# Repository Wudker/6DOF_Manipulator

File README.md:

# Educational 6-DOF Robotic Manipulator – Engineering Thesis

This project presents an educational anthropomorphic robotic manipulator with six degrees of freedom, developed as an engineering thesis. It combines mechanical design, kinematic analysis, embedded control, custom electronics and software development. The system uses an ESP32 and a custom PCB to control six stepper-driven joints through a local web interface. Forward and inverse kinematics provide position control, while repeatability and positioning tests were used to validate the adopted assumptions and identify the prototype’s mechanical limitations.

## Technologies

`ESP32` `C/C++` `Forward kinematics` `Inverse kinematics` `WebServer` `Stepper motors` `DRV8825` `Custom PCB` `Belt transmissions` `3D printing` `CAD`

## Usage and development status

After assembling the hardware and uploading the firmware, the manipulator can be controlled through its local web interface. Before starting movement, verify the wiring, power supply and initial joint positions. The prototype was successfully built and tested; potential improvements include increased mechanical stiffness, more accurate calibration and smoother trajectory planning.

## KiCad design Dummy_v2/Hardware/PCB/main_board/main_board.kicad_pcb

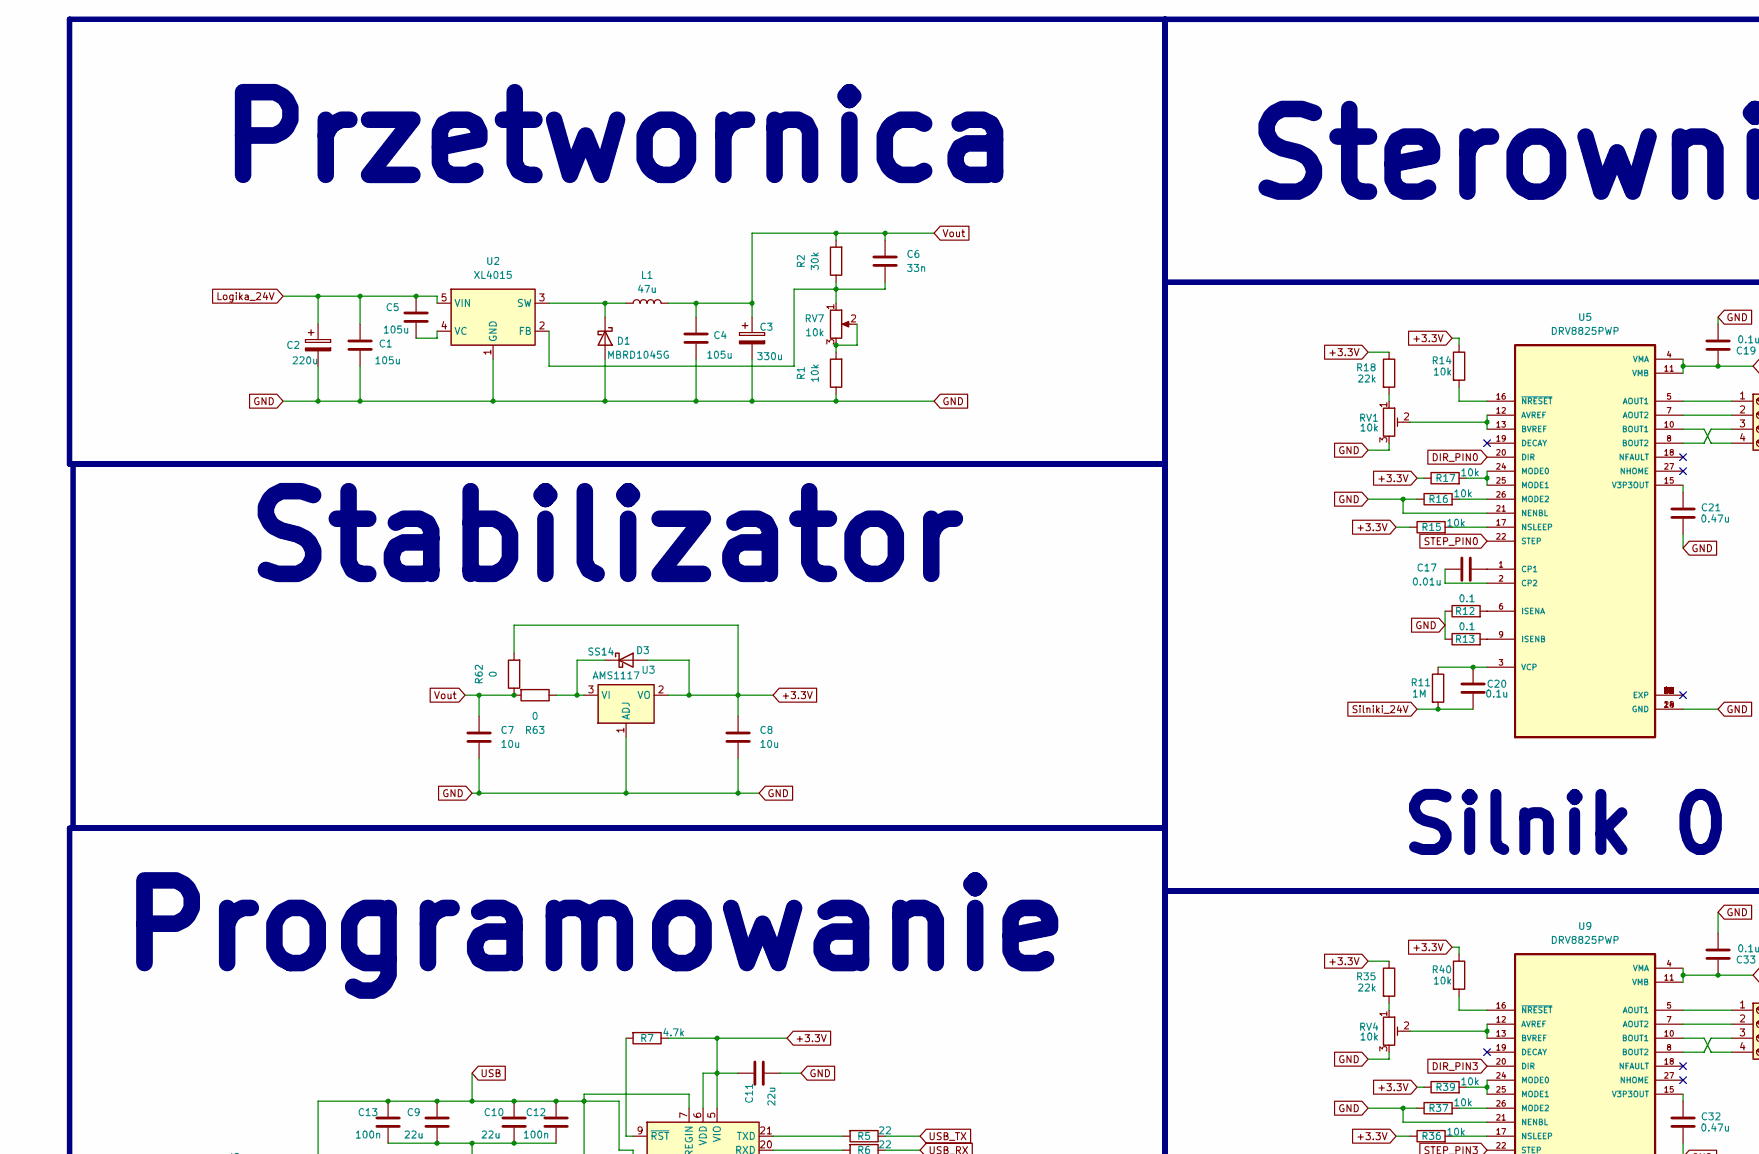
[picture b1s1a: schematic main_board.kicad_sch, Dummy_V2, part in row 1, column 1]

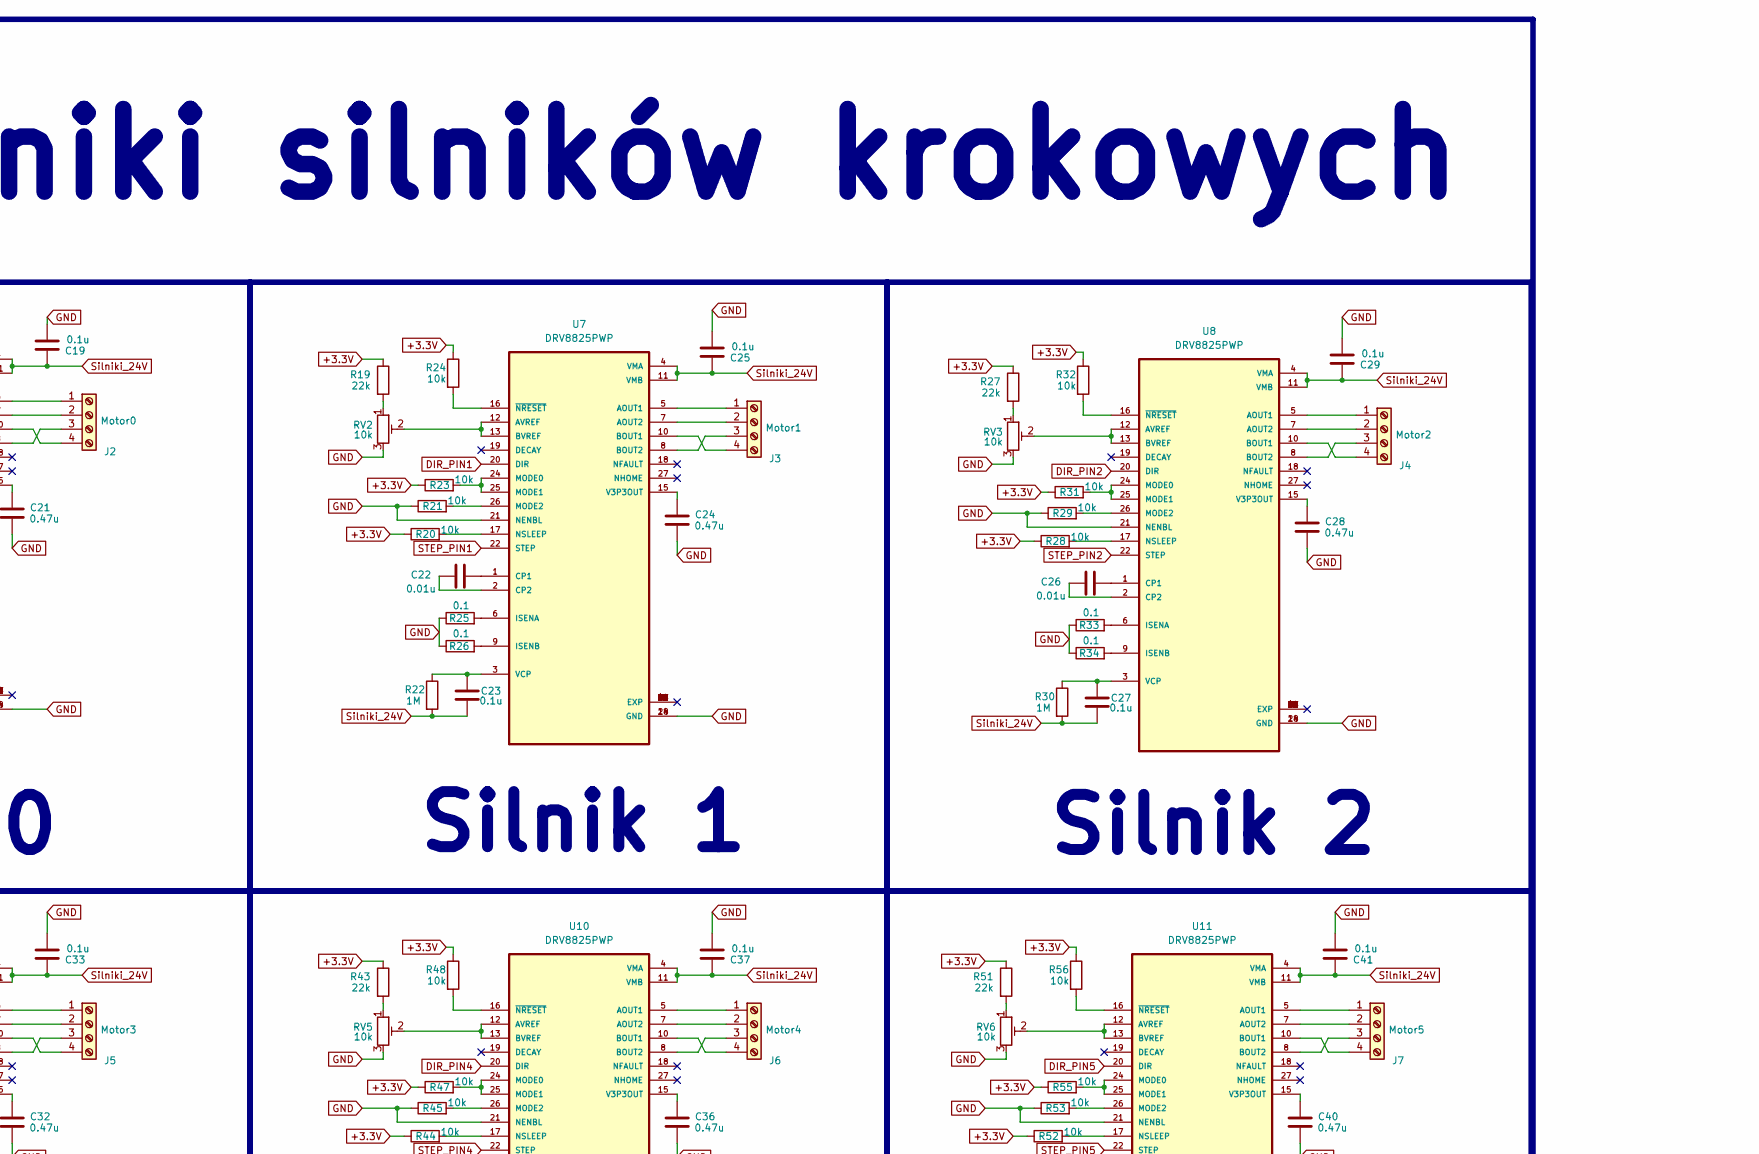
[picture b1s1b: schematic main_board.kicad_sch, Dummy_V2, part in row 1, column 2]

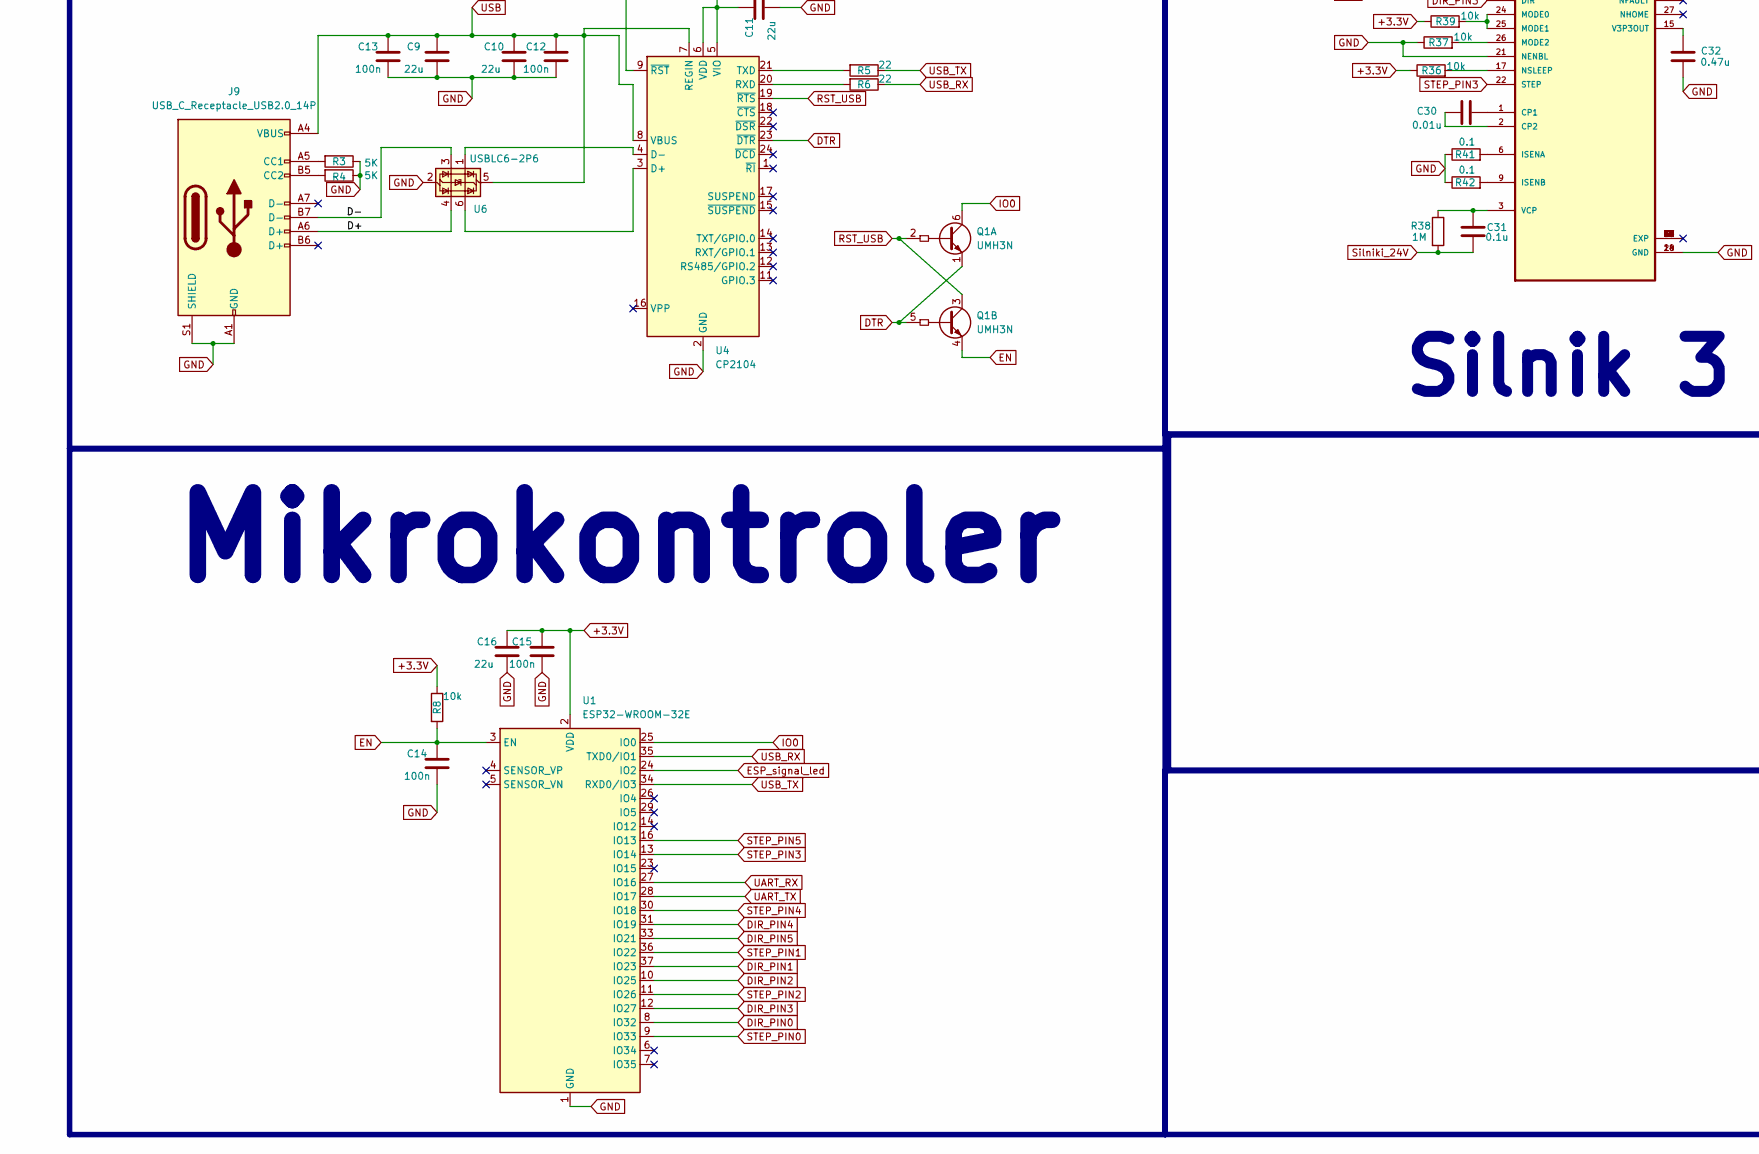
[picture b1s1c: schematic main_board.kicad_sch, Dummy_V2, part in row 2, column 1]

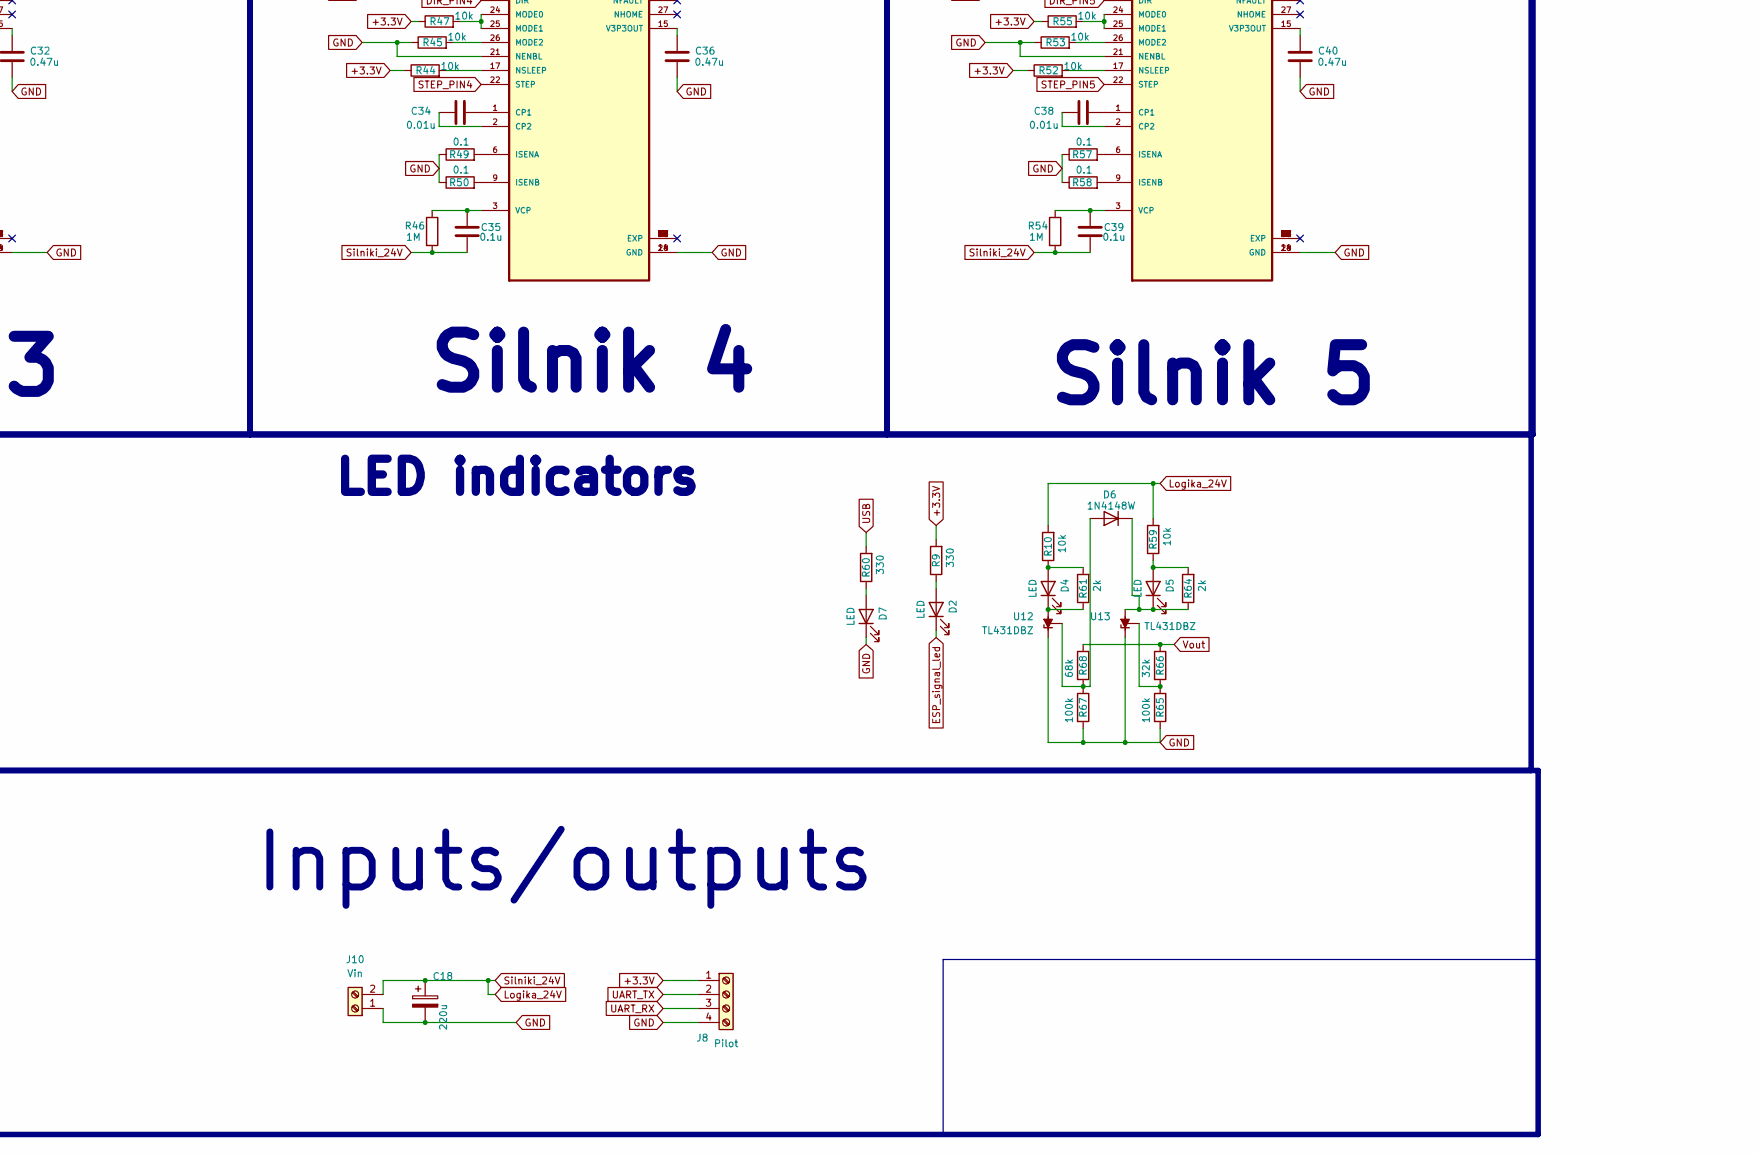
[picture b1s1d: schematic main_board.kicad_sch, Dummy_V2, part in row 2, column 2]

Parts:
C1, C4, C5: 105u; C_1206_3216Metric_Pad1.33x1.80mm_HandSolder
C2, C18: 220u; CP_Elec_10x14.3
C3: 330u; C_1206_3216Metric_Pad1.33x1.80mm_HandSolder
C6: 33n; C_1206_3216Metric_Pad1.33x1.80mm_HandSolder
C7, C8: 10u; C_1206_3216Metric_Pad1.33x1.80mm_HandSolder
C9, C10, C11, C16: 22u; C_1206_3216Metric_Pad1.33x1.80mm_HandSolder
C12, C13, C14, C15: 100n; C_1206_3216Metric_Pad1.33x1.80mm_HandSolder
C17, C22, C26, C30, C34, C38: 0.01u; C_1206_3216Metric_Pad1.33x1.80mm_HandSolder
C19, C20, C23, C25, C27, C29, C31, C33, C35, C37, C39, C41: 0.1u; C_1206_3216Metric_Pad1.33x1.80mm_HandSolder
C21, C24, C28, C32, C36, C40: 0.47u; C_1206_3216Metric_Pad1.33x1.80mm_HandSolder
D1: MBRD1045G; D_SOD-123
D2, D4, D5, D7: LED; LED_1206_3216Metric
D3: SS14; D_SMA
D6: 1N4148W; D_SOD-123
J2: Motor0; TerminalBlock_Phoenix_MPT-0,5-4-2.54_1x04_P2.54mm_Horizontal
J3: Motor1; TerminalBlock_Phoenix_MPT-0,5-4-2.54_1x04_P2.54mm_Horizontal
J4: Motor2; TerminalBlock_Phoenix_MPT-0,5-4-2.54_1x04_P2.54mm_Horizontal
J5: Motor3; TerminalBlock_Phoenix_MPT-0,5-4-2.54_1x04_P2.54mm_Horizontal
J6: Motor4; TerminalBlock_Phoenix_MPT-0,5-4-2.54_1x04_P2.54mm_Horizontal
J7: Motor5; TerminalBlock_Phoenix_MPT-0,5-4-2.54_1x04_P2.54mm_Horizontal
J8: Pilot; TerminalBlock_Phoenix_MPT-0,5-4-2.54_1x04_P2.54mm_Horizontal
J9: USB_C_Receptacle_USB2.0_14P; USB_C_Receptacle_G-Switch_GT-USB-7010ASV
J10: Vin; TerminalBlock_MetzConnect_Type055_RT01502HDWU_1x02_P5.00mm_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
L1: 47u; L_12x12mm_H4.5mm
Q1: UMH3N; SOT-363_SC-70-6
R1, R8, R10, R14, R15, R16, R17, R20, R21, R23, R24, R28, R29, R31, R32, R36, R37, R39, R40, R44, R45, R47, R48, R52, R53, R55, R56, R59: 10k; R_1206_3216Metric_Pad1.30x1.75mm_HandSolder
R2: 30k; R_1206_3216Metric_Pad1.30x1.75mm_HandSolder
R3, R4: 5K; R_1206_3216Metric_Pad1.30x1.75mm_HandSolder
R5, R6: 22; R_1206_3216Metric_Pad1.30x1.75mm_HandSolder
R7: 4.7k; R_1206_3216Metric_Pad1.30x1.75mm_HandSolder
R9, R60: 330; R_1206_3216Metric_Pad1.30x1.75mm_HandSolder
R11, R22, R30, R38, R46, R54: 1M; R_1206_3216Metric_Pad1.30x1.75mm_HandSolder
R12, R13, R25, R26, R33, R34, R41, R42, R49, R50, R57, R58: 0.1; R_1206_3216Metric_Pad1.30x1.75mm_HandSolder
R18, R19, R27, R35, R43, R51: 22k; R_1206_3216Metric_Pad1.30x1.75mm_HandSolder
R61, R64: 2k; R_1206_3216Metric_Pad1.30x1.75mm_HandSolder
R62, R63: 0; R_1206_3216Metric_Pad1.30x1.75mm_HandSolder
R65, R67: 100k; R_1206_3216Metric_Pad1.30x1.75mm_HandSolder
R66: 32k; R_1206_3216Metric_Pad1.30x1.75mm_HandSolder
R68: 68k; R_1206_3216Metric_Pad1.30x1.75mm_HandSolder
RV1, RV2, RV3, RV4, RV5, RV6: 10k; Potentiometer_Bourns_3314G_Vertical
RV7: 10k; Potentiometer_Bourns_3214J_Horizontal
U1: ESP32-WROOM-32E; ESP32-WROOM-32D
U2: XL4015; TO-263-5_TabPin3
U3: AMS1117; SOT-223-3_TabPin2
U4: CP2104; QFN-24-1EP_4x4mm_P0.5mm_EP2.6x2.6mm
U5, U7, U8, U9, U10, U11: DRV8825PWP; IC_TPS61196PWPRQ1
U6: USBLC6-2P6; SOT-666
U12, U13: TL431DBZ; SOT-23

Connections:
+3.3V: C8.1, C11.1, C15.1, C16.1, D3.2 (A), J8.1, R7.1, R8.1, R9.2, R14.1, R15.1, R17.1, R18.1, R19.1, R20.1, R23.1, R24.1, R27.1, R28.1, R31.1, R32.1, R35.1, R36.1, R39.1, R40.1, R43.1, R44.1, R47.1, R48.1, R51.1, R52.1, R55.1, R56.1, R62.2, U1.2 (VDD), U3.2 (VO), U4.5 (VIO), U4.6 (VDD)
/D+: J9.A6 (D+), U6.4 (I/O2)
/D-: J9.B7 (D-), U6.3 (I/O2)
DIR_PIN0: U1.8 (IO32), U5.20 (DIR)
DIR_PIN1: U1.37 (IO23), U7.20 (DIR)
DIR_PIN2: U1.10 (IO25), U8.20 (DIR)
DIR_PIN3: U1.12 (IO27), U9.20 (DIR)
DIR_PIN4: U1.31 (IO19), U10.20 (DIR)
DIR_PIN5: U1.33 (IO21), U11.20 (DIR)
DTR: Q1.1 (E1), Q1.5 (B2), U4.23 (~DTR)
EN: C14.1, Q1.4 (E2), R8.2, U1.3 (EN)
ESP_signal_led: D2.1 (K), U1.24 (IO2)
GND: C1.2, C2.2, C3.2, C4.2, C7.2, C8.2, C9.2, C10.2, C11.2, C12.2, C13.2, C14.2, C15.2, C16.2, C18.2, C19.1, C21.1, C24.1, C25.1, C28.1, C29.1, C32.1, C33.1, C36.1, C37.1, C40.1, C41.1, D1.2 (A), D7.1 (K), J8.4, J9.A1 (GND), J9.A12 (GND), J9.B1 (GND), J9.B12 (GND), J9.S1 (SHIELD), J10.1, R1.1, R3.1, R4.1, R12.1, R13.1, R16.1, R21.1, R25.1, R26.1, R29.1, R33.1, R34.1, R37.1, R41.1, R42.1, R45.1, R49.1, R50.1, R53.1, R57.1, R58.1, R65.2, R67.2, RV1.3, RV2.3, RV3.3, RV4.3, RV5.3, RV6.3, U1.1 (GND), U1.15 (GND), U1.38 (GND), U1.39 (GND), U2.1 (GND), U3.1 (ADJ), U4.2 (GND), U4.25 (GND), U5.14 (GND), U5.21 (NENBL), U5.28 (GND), U6.2 (GND), U7.14 (GND), U7.21 (NENBL), U7.28 (GND), U8.14 (GND), U8.21 (NENBL), U8.28 (GND), U9.14 (GND), U9.21 (NENBL), U9.28 (GND), U10.14 (GND), U10.21 (NENBL), U10.28 (GND), U11.14 (GND), U11.21 (NENBL), U11.28 (GND), U12.1 (K), U13.1 (K)
IO0: Q1.6 (C1), U1.25 (IO0)
Logika_24V: C1.1, C2.1, C5.1, C18.1, C19.2, C20.2, C23.2, C25.2, C27.2, C29.2, C31.2, C33.2, C35.2, C37.2, C39.2, C41.2, J10.2, R10.2, R11.2, R22.2, R30.2, R38.2, R46.2, R54.2, R59.2, U2.5 (VIN), U5.4 (VMA), U5.11 (VMB), U7.4 (VMA), U7.11 (VMB), U8.4 (VMA), U8.11 (VMB), U9.4 (VMA), U9.11 (VMB), U10.4 (VMA), U10.11 (VMB), U11.4 (VMA), U11.11 (VMB)
unnamed: D1.1 (K), L1.1, U2.3 (SW)
unnamed: D2.2 (A), R9.1
unnamed: D3.1 (K), R63.1, U3.3 (VI)
unnamed: D4.2 (A), R10.1, R61.2
unnamed: D4.1 (K), R61.1, U12.3 (A)
unnamed: D5.2 (A), R59.1, R64.2
unnamed: D5.1 (K), D6.1 (K), R64.1, U13.3 (A)
unnamed: D6.2 (A), R67.1, R68.2, U12.2 (REF)
unnamed: D7.2 (A), R60.1
unnamed: J2.1, U5.5 (AOUT1)
unnamed: J2.2, U5.7 (AOUT2)
unnamed: J2.3, U5.8 (BOUT2)
unnamed: J2.4, U5.10 (BOUT1)
unnamed: J3.1, U7.5 (AOUT1)
unnamed: J3.2, U7.7 (AOUT2)
unnamed: J3.3, U7.8 (BOUT2)
unnamed: J3.4, U7.10 (BOUT1)
unnamed: J4.1, U8.5 (AOUT1)
unnamed: J4.2, U8.7 (AOUT2)
unnamed: J4.3, U8.8 (BOUT2)
unnamed: J4.4, U8.10 (BOUT1)
unnamed: J5.1, U9.5 (AOUT1)
unnamed: J5.2, U9.7 (AOUT2)
unnamed: J5.3, U9.8 (BOUT2)
unnamed: J5.4, U9.10 (BOUT1)
unnamed: J6.1, U10.5 (AOUT1)
unnamed: J6.2, U10.7 (AOUT2)
unnamed: J6.3, U10.8 (BOUT2)
unnamed: J6.4, U10.10 (BOUT1)
unnamed: J7.1, U11.5 (AOUT1)
unnamed: J7.2, U11.7 (AOUT2)
unnamed: J7.3, U11.8 (BOUT2)
unnamed: J7.4, U11.10 (BOUT1)
unnamed: J9.A5 (CC1), R3.2
unnamed: J9.B5 (CC2), R4.2
unnamed: R1.2, RV7.2, RV7.3
unnamed: R18.2, RV1.1
unnamed: R19.2, RV2.1
unnamed: R27.2, RV3.1
unnamed: R35.2, RV4.1
unnamed: R43.2, RV5.1
unnamed: R51.2, RV6.1
unnamed: C6.2, R2.1, RV7.1, U2.2 (FB)
unnamed: C5.2, U2.4 (VC)
unnamed: U4.3 (D+), U6.6 (I/O1)
unnamed: U4.4 (D-), U6.1 (I/O1)
unnamed: R6.2, U4.20 (RXD)
unnamed: R5.2, U4.21 (TXD)
unnamed: R7.2, U4.9 (~RST)
unnamed: RV1.2, U5.12 (AVREF), U5.13 (BVREF)
unnamed: C17.1, U5.1 (CP1)
unnamed: C17.2, U5.2 (CP2)
unnamed: R12.2, U5.6 (ISENA)
unnamed: R13.2, U5.9 (ISENB)
unnamed: R17.2, U5.24 (MODE0), U5.25 (MODE1)
unnamed: R16.2, U5.26 (MODE2)
unnamed: R15.2, U5.17 (NSLEEP)
unnamed: C21.2, U5.15 (V3P3OUT)
unnamed: C20.1, R11.1, U5.3 (VCP)
unnamed: R14.2, U5.16 (~NRESET)
unnamed: RV2.2, U7.12 (AVREF), U7.13 (BVREF)
unnamed: C22.1, U7.1 (CP1)
unnamed: C22.2, U7.2 (CP2)
unnamed: R25.2, U7.6 (ISENA)
unnamed: R26.2, U7.9 (ISENB)
unnamed: R23.2, U7.24 (MODE0), U7.25 (MODE1)
unnamed: R21.2, U7.26 (MODE2)
unnamed: R20.2, U7.17 (NSLEEP)
unnamed: C24.2, U7.15 (V3P3OUT)
unnamed: C23.1, R22.1, U7.3 (VCP)
unnamed: R24.2, U7.16 (~NRESET)
unnamed: RV3.2, U8.12 (AVREF), U8.13 (BVREF)
unnamed: C26.1, U8.1 (CP1)
unnamed: C26.2, U8.2 (CP2)
unnamed: R33.2, U8.6 (ISENA)
unnamed: R34.2, U8.9 (ISENB)
unnamed: R31.2, U8.24 (MODE0), U8.25 (MODE1)
unnamed: R29.2, U8.26 (MODE2)
unnamed: R28.2, U8.17 (NSLEEP)
unnamed: C28.2, U8.15 (V3P3OUT)
unnamed: C27.1, R30.1, U8.3 (VCP)
unnamed: R32.2, U8.16 (~NRESET)
unnamed: RV4.2, U9.12 (AVREF), U9.13 (BVREF)
unnamed: C30.1, U9.1 (CP1)
unnamed: C30.2, U9.2 (CP2)
unnamed: R41.2, U9.6 (ISENA)
unnamed: R42.2, U9.9 (ISENB)
unnamed: R39.2, U9.24 (MODE0), U9.25 (MODE1)
unnamed: R37.2, U9.26 (MODE2)
unnamed: R36.2, U9.17 (NSLEEP)
unnamed: C32.2, U9.15 (V3P3OUT)
unnamed: C31.1, R38.1, U9.3 (VCP)
unnamed: R40.2, U9.16 (~NRESET)
unnamed: RV5.2, U10.12 (AVREF), U10.13 (BVREF)
unnamed: C34.1, U10.1 (CP1)
unnamed: C34.2, U10.2 (CP2)
unnamed: R49.2, U10.6 (ISENA)
unnamed: R50.2, U10.9 (ISENB)
unnamed: R47.2, U10.24 (MODE0), U10.25 (MODE1)
unnamed: R45.2, U10.26 (MODE2)
unnamed: R44.2, U10.17 (NSLEEP)
unnamed: C36.2, U10.15 (V3P3OUT)
unnamed: C35.1, R46.1, U10.3 (VCP)
unnamed: R48.2, U10.16 (~NRESET)
unnamed: RV6.2, U11.12 (AVREF), U11.13 (BVREF)
unnamed: C38.1, U11.1 (CP1)
unnamed: C38.2, U11.2 (CP2)
unnamed: R57.2, U11.6 (ISENA)
unnamed: R58.2, U11.9 (ISENB)
unnamed: R55.2, U11.24 (MODE0), U11.25 (MODE1)
unnamed: R53.2, U11.26 (MODE2)
unnamed: R52.2, U11.17 (NSLEEP)
unnamed: C40.2, U11.15 (V3P3OUT)
unnamed: C39.1, R54.1, U11.3 (VCP)
unnamed: R56.2, U11.16 (~NRESET)
unnamed: R65.1, R66.2, U13.2 (REF)
RST_USB: Q1.2 (B1), Q1.3 (C2), U4.19 (~RTS)
STEP_PIN0: U1.9 (IO33), U5.22 (STEP)
STEP_PIN1: U1.36 (IO22), U7.22 (STEP)
STEP_PIN2: U1.11 (IO26), U8.22 (STEP)
STEP_PIN3: U1.13 (IO14), U9.22 (STEP)
STEP_PIN4: U1.30 (IO18), U10.22 (STEP)
STEP_PIN5: U1.16 (IO13), U11.22 (STEP)
UART_RX: J8.3, U1.27 (IO16)
UART_TX: J8.2, U1.28 (IO17)
USB: C9.1, C10.1, C12.1, C13.1, J9.A4 (VBUS), J9.A9 (VBUS), J9.B4 (VBUS), J9.B9 (VBUS), R60.2, U4.7 (REGIN), U4.8 (VBUS), U6.5 (VBUS)
USB_RX: R6.1, U1.35 (TXD0/IO1)
USB_TX: R5.1, U1.34 (RXD0/IO3)
Vout: C3.1, C4.1, C6.1, C7.1, L1.2, R2.2, R62.1, R63.2, R66.1, R68.1

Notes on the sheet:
Programowanie
Mikrokontroler
Inputs/outputs
LED indicators
Sterowniki silników krokowych
Stabilizator
Silnik 1
Silnik 2
Silnik 0
Przetwornica
Silnik 4
Silnik 3
Silnik 5

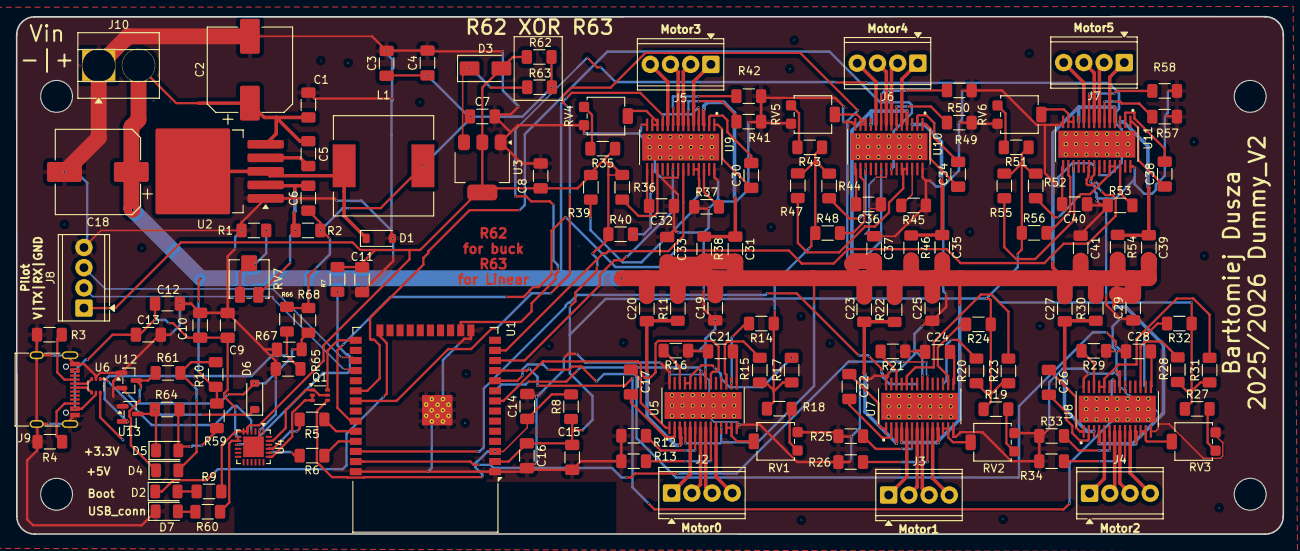
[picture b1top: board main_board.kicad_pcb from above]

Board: 2 copper layers, 159.2 x 65.0 mm, 147 parts (0 on the bottom side), 144 nets.

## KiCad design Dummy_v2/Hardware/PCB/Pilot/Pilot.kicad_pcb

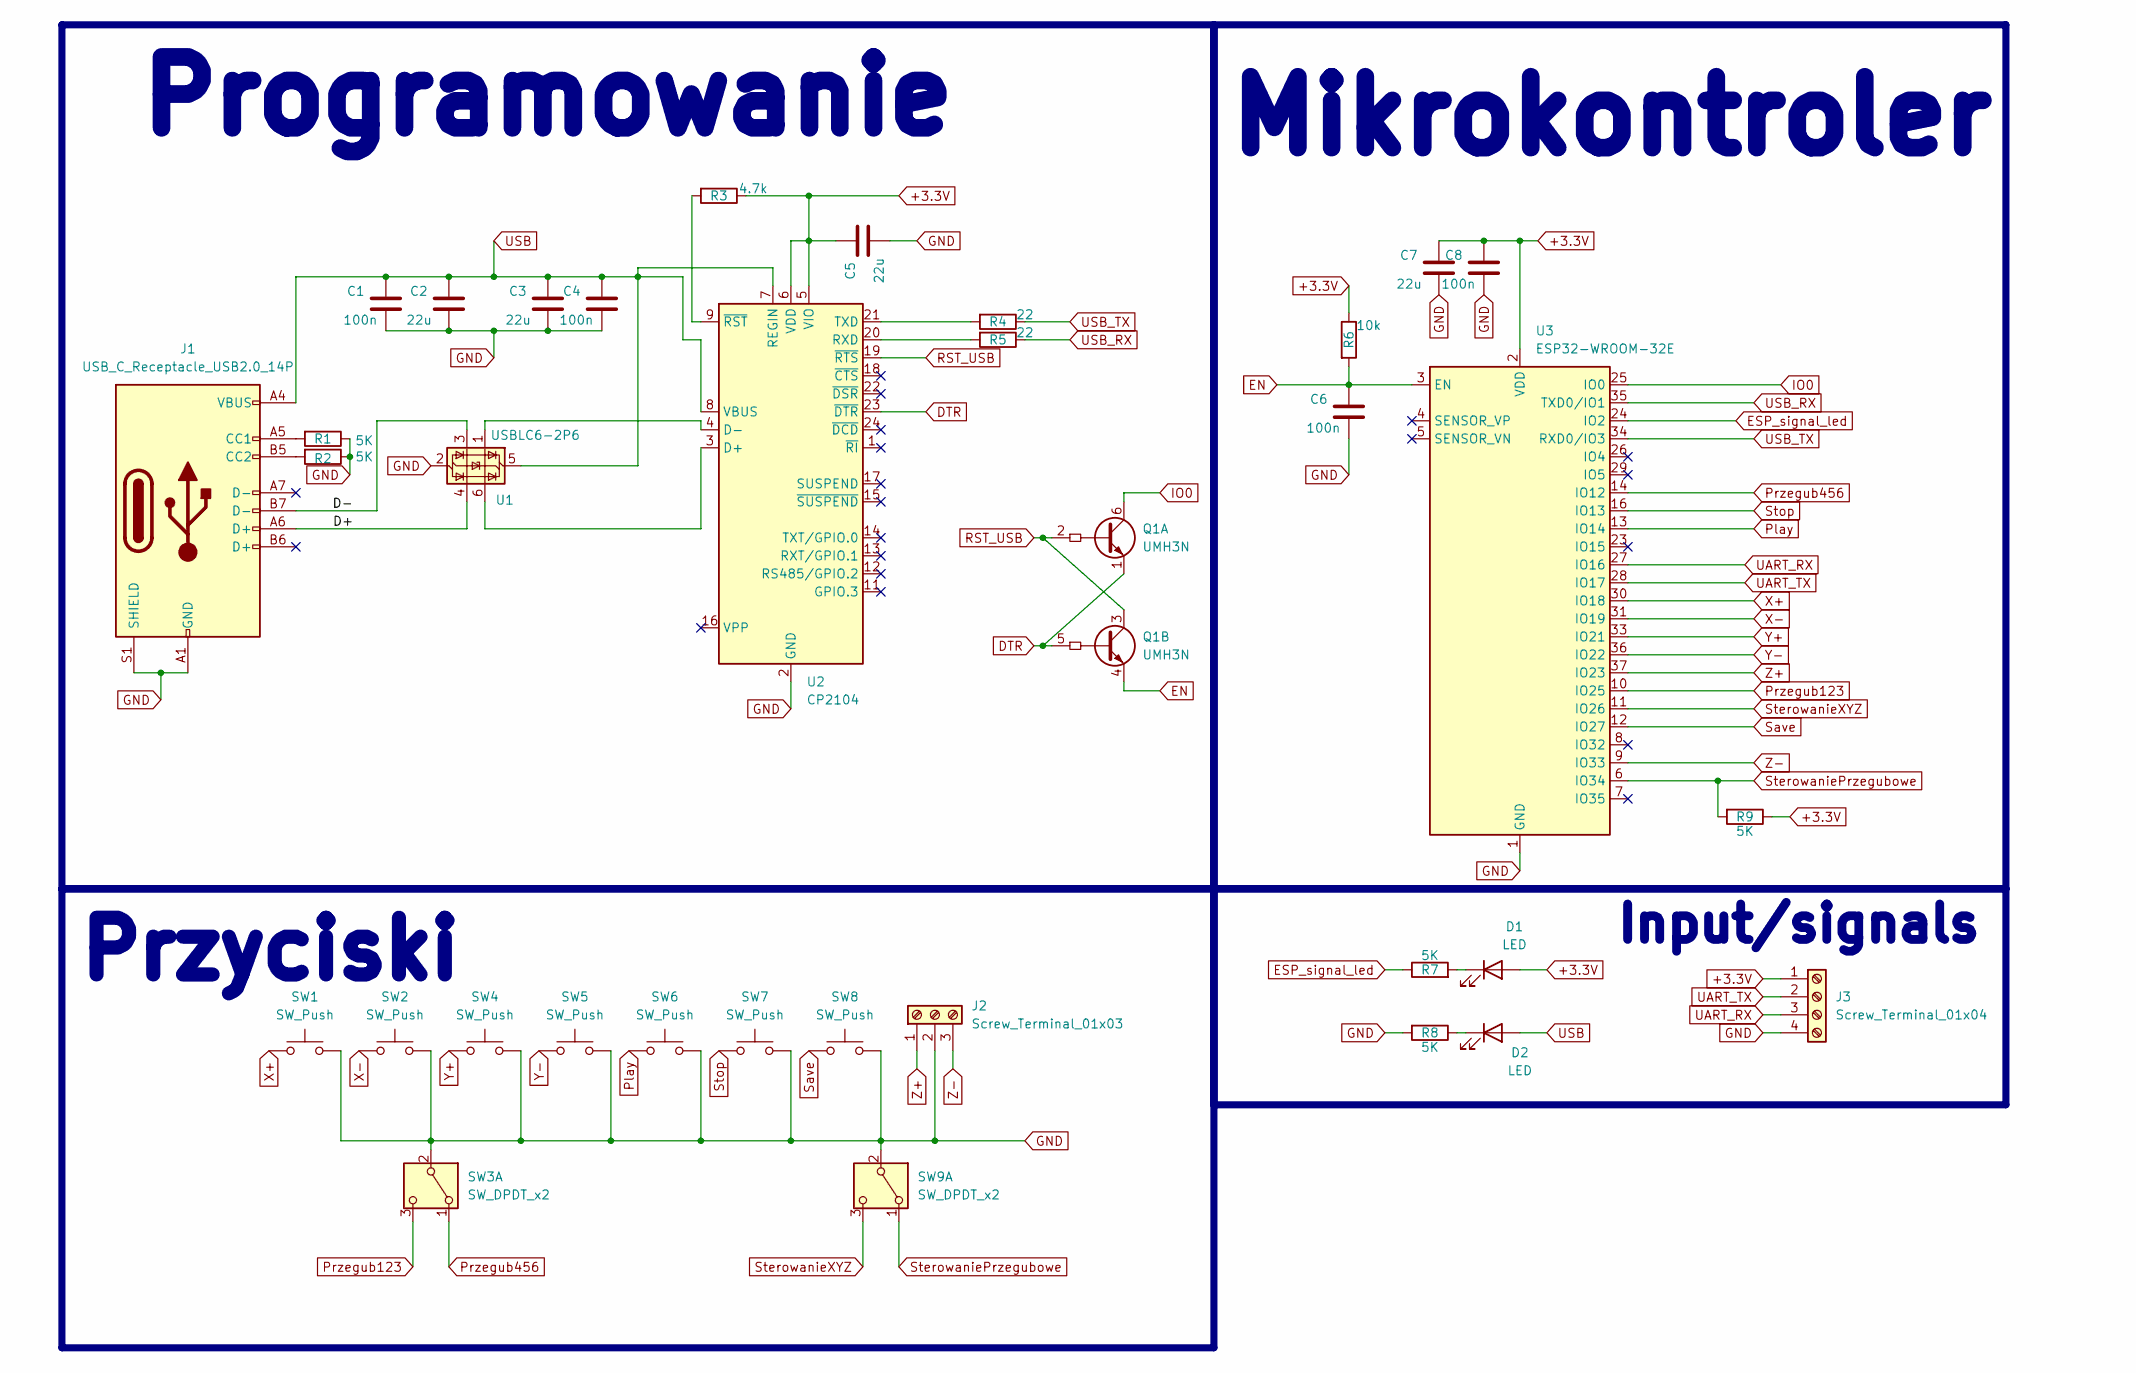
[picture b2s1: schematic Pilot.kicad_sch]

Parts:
C1, C4, C6, C8: 100n; C_1206_3216Metric_Pad1.33x1.80mm_HandSolder
C2, C3, C5, C7: 22u; C_1206_3216Metric_Pad1.33x1.80mm_HandSolder
D1, D2: LED; LED_1206_3216Metric
J1: USB_C_Receptacle_USB2.0_14P; USB_C_Receptacle_GCT_USB4105-xx-A_16P_TopMnt_Horizontal
J2: Screw_Terminal_01x03; TerminalBlock_MaiXu_MX126-5.0-03P_1x03_P5.00mm
J3: Screw_Terminal_01x04; TerminalBlock_MaiXu_MX126-5.0-04P_1x04_P5.00mm
Q1: UMH3N; SOT-363_SC-70-6
R1, R2, R7, R8, R9: 5K; R_1206_3216Metric_Pad1.30x1.75mm_HandSolder
R3: 4.7k; R_1206_3216Metric_Pad1.30x1.75mm_HandSolder
R4, R5: 22; R_1206_3216Metric_Pad1.30x1.75mm_HandSolder
R6: 10k; R_1206_3216Metric_Pad1.30x1.75mm_HandSolder
SW1, SW2, SW4, SW5, SW6, SW7, SW8: SW_Push; SW_Push_1P1T_NO_CK_KSC6xxJ
SW3, SW9: SW_DPDT_x2; SW_CK_JS202011CQN_DPDT_Straight
U1: USBLC6-2P6; SOT-666
U2: CP2104; QFN-24-1EP_4x4mm_P0.5mm_EP2.6x2.6mm
U3: ESP32-WROOM-32E; ESP32-WROOM-32D

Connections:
+3.3V: C5.1, C7.1, C8.1, D1.2 (A), J3.1, R3.1, R6.1, R9.1, U2.5 (VIO), U2.6 (VDD), U3.2 (VDD)
/D+: J1.A6 (D+), U1.4 (I/O2)
/D-: J1.B7 (D-), U1.3 (I/O2)
DTR: Q1.1 (E1), Q1.5 (B2), U2.23 (~DTR)
EN: C6.1, Q1.4 (E2), R6.2, U3.3 (EN)
ESP_signal_led: R7.1, U3.24 (IO2)
GND: C1.2, C2.2, C3.2, C4.2, C5.2, C6.2, C7.2, C8.2, J1.A1 (GND), J1.A12 (GND), J1.B1 (GND), J1.B12 (GND), J1.S1 (SHIELD), J2.2, J3.4, R1.1, R2.1, R8.2, SW1.2, SW2.2, SW3.2 (B), SW4.2, SW5.2, SW6.2, SW7.2, SW8.2, SW9.2 (B), U1.2 (GND), U2.2 (GND), U2.25 (GND), U3.1 (GND), U3.15 (GND), U3.38 (GND), U3.39 (GND)
IO0: Q1.6 (C1), U3.25 (IO0)
unnamed: D1.1 (K), R7.2
unnamed: D2.1 (K), R8.1
unnamed: J1.A5 (CC1), R1.2
unnamed: J1.B5 (CC2), R2.2
unnamed: U1.6 (I/O1), U2.3 (D+)
unnamed: U1.1 (I/O1), U2.4 (D-)
unnamed: R5.2, U2.20 (RXD)
unnamed: R4.2, U2.21 (TXD)
unnamed: R3.2, U2.9 (~RST)
Play: SW6.1, U3.13 (IO14)
Przegub123: SW3.3 (C), U3.10 (IO25)
Przegub456: SW3.1 (A), U3.14 (IO12)
RST_USB: Q1.2 (B1), Q1.3 (C2), U2.19 (~RTS)
Save: SW8.1, U3.12 (IO27)
SterowaniePrzegubowe: R9.2, SW9.1 (A), U3.6 (IO34)
SterowanieXYZ: SW9.3 (C), U3.11 (IO26)
Stop: SW7.1, U3.16 (IO13)
UART_RX: J3.3, U3.27 (IO16)
UART_TX: J3.2, U3.28 (IO17)
USB: C1.1, C2.1, C3.1, C4.1, D2.2 (A), J1.A4 (VBUS), J1.A9 (VBUS), J1.B4 (VBUS), J1.B9 (VBUS), U1.5 (VBUS), U2.7 (REGIN), U2.8 (VBUS)
USB_RX: R5.1, U3.35 (TXD0/IO1)
USB_TX: R4.1, U3.34 (RXD0/IO3)
X+: SW1.1, U3.30 (IO18)
X-: SW2.1, U3.31 (IO19)
Y+: SW4.1, U3.33 (IO21)
Y-: SW5.1, U3.36 (IO22)
Z+: J2.1, U3.37 (IO23)
Z-: J2.3, U3.9 (IO33)

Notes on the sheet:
Przyciski
Programowanie
Input/signals
Mikrokontroler

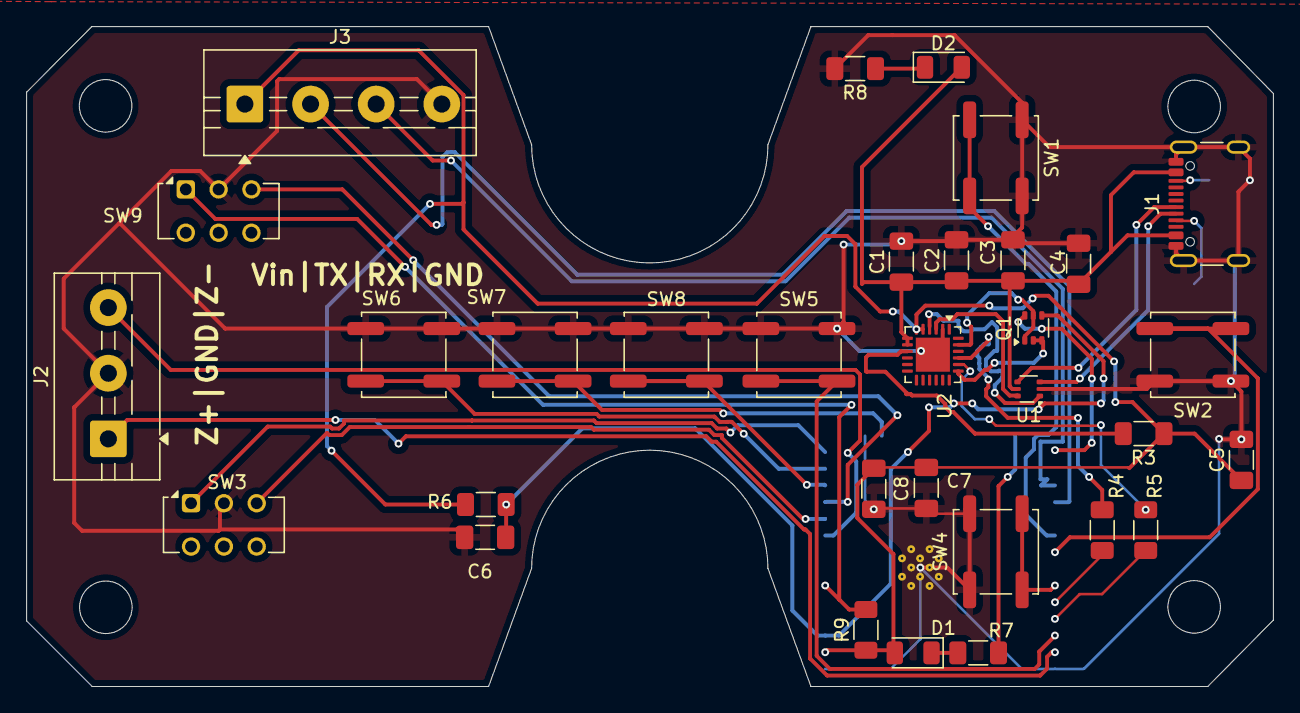
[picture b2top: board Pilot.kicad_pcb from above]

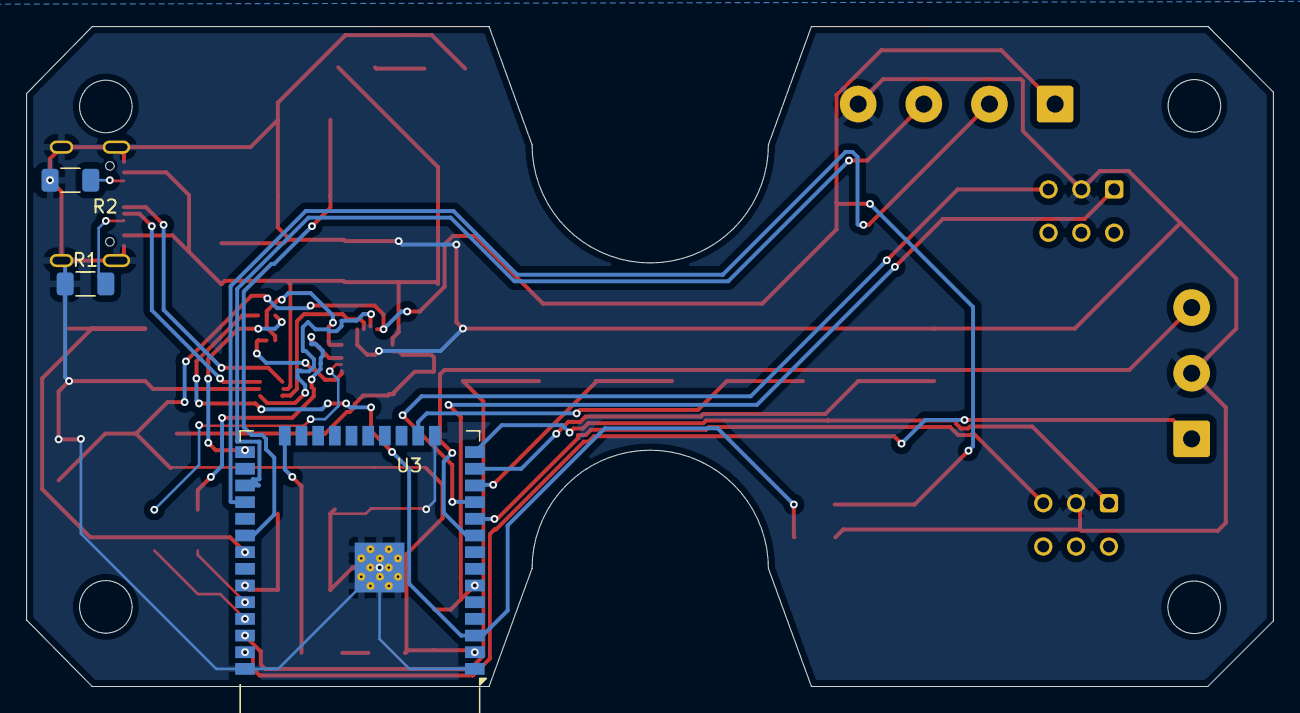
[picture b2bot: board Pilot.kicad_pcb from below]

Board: 2 copper layers, 95.0 x 50.3 mm, 35 parts (3 on the bottom side), 36 nets.

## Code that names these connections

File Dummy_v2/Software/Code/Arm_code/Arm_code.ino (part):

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static const float DH_theta_off_deg[3]= { 0.0f,      90.0f,      0.0f };

// UART (pilot)
#define UART_RX 16
#define UART_TX 17
HardwareSerial& LINK = Serial2;
static const uint32_t BAUD = 9600;

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#define LED_PIN 2

// PINY DRV
#define STEP_PIN0 33
#define DIR_PIN0  32
#define STEP_PIN1 22
#define DIR_PIN1  23
#define STEP_PIN2 26
#define DIR_PIN2  25
#define STEP_PIN3 14
#define DIR_PIN3  27
#define STEP_PIN4 18
#define DIR_PIN4  19
#define STEP_PIN5 13
#define DIR_PIN5  21

const int STEP_PINS[NUM_STEPPERS] = { STEP_PIN0, STEP_PIN1, STEP_PIN2, STEP_PIN3, STEP_PIN4, STEP_PIN5 };
const int DIR_PINS [NUM_STEPPERS] = { DIR_PIN0,  DIR_PIN1,  DIR_PIN2,  DIR_PIN3,  DIR_PIN4,  DIR_PIN5  };

// Przełożenia: obr./silnika na obr./przegubu
const float GEAR[NUM_STEPPERS] = { 6.0f, 6.0f, 4.0f, 2.0f, 2.0f, 1.0f };
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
